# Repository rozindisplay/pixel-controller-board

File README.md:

# pixel-controller-board
EDA: [KiCad](https://www.kicad.org/) (5.1.10)

The schematics and PCB layout for the pixel-node controller board

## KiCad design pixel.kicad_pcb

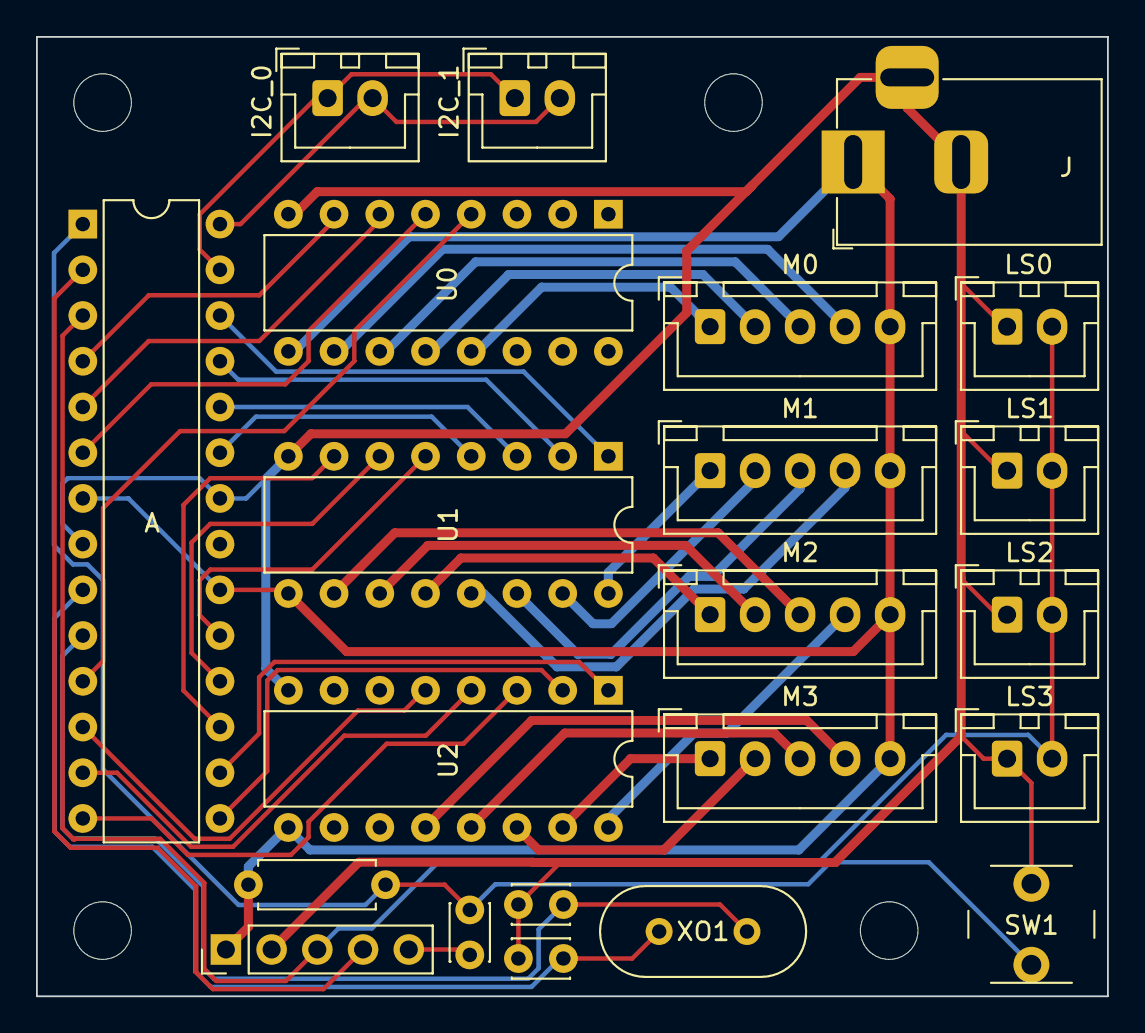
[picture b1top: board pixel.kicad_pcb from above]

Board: 2 copper layers, 59.5 x 53.3 mm, 22 parts (0 on the bottom side), 42 nets.

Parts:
A: ATmega328P; DIP-28_W7.62mm
C0, C1: 22pF; C_Disc_D3.0mm_W2.0mm_P2.50mm
C3: 0.1uf; C_Disc_D3.0mm_W2.0mm_P2.50mm
I2C_0, I2C_1: I2C; JST_XH_B2B-XH-A_1x02_P2.50mm_Vertical
J: Barrel_Jack_MountingPin; BarrelJack_Horizontal
LS0, LS1, LS2, LS3: Limit Switch; JST_XH_B2B-XH-A_1x02_P2.50mm_Vertical
M0, M1, M2, M3: 28BYJ-48; JST_XH_B5B-XH-A_1x05_P2.50mm_Vertical
PP1: PROGRAM_PORT; PinHeader_1x05_P2.54mm_Vertical
R1: 10K Ohm; R_Axial_DIN0207_L6.3mm_D2.5mm_P7.62mm_Horizontal
SW1: PUSH_RESET; SW_PUSH_6mm_2pin
U0, U1, U2: ULN2003; DIP-16_W7.62mm
XO1: 16MHz; Crystal_HC49-4H_Vertical

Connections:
+5V: A.7, A.20, J.1, M0.5, M1.5, M2.5, M3.5, PP1.1, R1.1, U0.9, U1.9, U2.9
GND: A.8, A.22, C0.1, C1.2, J.2, J.3, LS0.1, LS1.1, LS2.1, LS3.1, PP1.2, SW1.2, U0.8, U1.8, U2.8
unnamed: A.1, C3.1, R1.2, SW1.1
unnamed: A.2, PP1.4
unnamed: A.3, LS0.2, LS1.2, LS2.2, LS3.2, PP1.3
unnamed: A.4, U0.7
unnamed: A.5, U0.6
unnamed: A.6, U0.5
unnamed: A.9, C1.1, XO1.2
unnamed: A.10, C0.2, XO1.1
unnamed: A.11, U0.4
unnamed: A.12, U2.5
unnamed: A.13, U2.4
unnamed: A.14, U2.3
unnamed: A.15, U2.2
unnamed: A.16, U2.1
unnamed: A.17, U1.7
unnamed: A.18, U1.6
unnamed: A.19, U1.5
unnamed: A.23, U1.4
unnamed: A.24, U1.3
unnamed: A.25, U1.2
unnamed: A.26, U1.1
unnamed: A.27, I2C_0.1, I2C_1.1
unnamed: A.28, I2C_0.2, I2C_1.2
unnamed: C3.2, PP1.5
unnamed: M0.1, U0.13
unnamed: M0.2, U0.12
unnamed: M0.3, U0.11
unnamed: M0.4, U0.10
unnamed: M1.1, U1.16
unnamed: M1.2, U1.15
unnamed: M1.3, U1.14
unnamed: M1.4, U1.13
unnamed: M2.1, U1.12
unnamed: M2.2, U1.11
unnamed: M2.3, U1.10
unnamed: M2.4, U2.16
unnamed: M3.1, U2.15
unnamed: M3.2, U2.14
unnamed: M3.3, U2.13
unnamed: M3.4, U2.12

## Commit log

2021-07-14 init
2021-07-17 updated board
2021-07-17 renamed pixle to pixel
